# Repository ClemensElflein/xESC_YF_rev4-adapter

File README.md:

<!-- PROJECT SHIELDS -->
<!--
- Markdown "reference style" links for readability.
- Reference links are enclosed in brackets [ ] instead of parentheses ( ).
  (See the bottom of this document for the declaration of the reference variables)
-->
[![Contributors][contributors-shield]][contributors-url]
[![Forks][forks-shield]][forks-url]
[![Stargazers][stars-shield]][stars-url]
[![Issues][issues-shield]][issues-url]
[![MIT License][license-shield]][license-url]

<!-- PROJECT LOGO -->
<br />
<div align="center">
<h3 align="center">xESC YardForce (Rev4) adapter for <a href="https://github.com/ClemensElflein/OpenMower">OpenMower</a></h3>

  <p align="center">
    Simple xESC adapter for stock Rev4 (built 2017) blade-motor<br>
    (the one with a internal motor controller under his cap)
    <br />
  </p>

  |             v1.x Hardware              |             v2.x Hardware              |
  | :------------------------------------: | :------------------------------------: |
  |  |  |

</div>

<!-- ABOUT THE PROJECT -->
## About The Project

Those who want use <a href="https://github.com/ClemensElflein/OpenMower">OpenMower</a> with an older YardForce "Rev. 4" (built 2017) model, fail with the stock Blade-Motor as it has an embedded motor-controller under it's cap.

It's not very difficult to use this motor:
- Remove stock driver controller
- Wire the coil cables directly
- Add a 5 pin cable to the motor hall sensors
- Connect them to OM's mow-motor-hall-input plug
and use OM's xESC.

But it's somehow "crafted" and you need to be capable to do these things.

As an alternative, this "Adapter" is thought to replace OM's default Mow- xESC.<br>
In addition to this adapter, it's nevertheless **required to exchange two cables of the mow motor cabling**. But this should be also possible for the untalented (see [Requirements](#requirements)).

<p align="right">(<a href="#readme-top">back to top</a>)</p>

## Requirements

**It's mandatory to cross the green and black mow-motor-cables!**

> [!WARNING]  
> **Never** plug or un-plug the mow-motor while the adapter is powered!

> [!WARNING]  
> Do **not** simply trust the cable colors!<br>
> Check the image and validate if your
> cables do have the same colors! If not adapt accordingly

Either exchange the pins within the plug, or do it the lazy way like me, with a luster terminal.
The latter has the advantage that you immediately see that you already crossed green/black.

## Prerequisites

* The compiled firmware, which can be found within the [Actions](https://github.com/ClemensElflein/xESC_YF_rev4-adapter/actions) section. Click the one you're intersted in (newest or tagged), scroll down to 'Artifacts', download and unzip to somewhere.
* As of writing, your openmower image has to be on edge version >= commit [0bfd489](https://github.com/ClemensElflein/open_mower_ros/commit/0bfd489401b3e659d183e6c1f9b557cb0d59d3c1) which happened on 2024-07-04

## Firmware Installation

### Requirements

* You need an ST-Link debugger/programmer, like one of the cheap "ST-Link V2" probes from one of the big online retailer.
* [STLINK Tools](https://github.com/stlink-org/stlink) >= v1.8.0 (earlier versions do **not** support the used STM32C0x MCU)

### Hardware Version Branding

Starting with hardware version 2.0, the adapters MCU needs to be branded by flashing a hardware config into the OTP area.

#### Branding Process:

1. **Generate** Hardware Config Binaries

   ```bash
   cd firmware/host-hw-config
   lbuild build
   scons
   ```

   This creates i.e.:
   - `hw_config_v1.0.bin` - Hardware v1.0 configuration
   - `hw_config_v2.0.bin` - Hardware v2.0 configuration
  
1. **Connect your ST-Link** to the adapter PCB. Do **not** connect the 3.3V pin if your adapter is already assembled to the OpenMower Mainboard and get powered by it!

1. **Flash** Hardware Config

   ```bash
   # Flash/Brand v2.0 config with ST-Link/V2
   STM32_Programmer_CLI -c port=SWD -d hw_config_v2.0.bin 0x1FFF7000
   ```

The branding process writes a small hardware information structure to the first two OTP dwords. **Take attention** that OTP flash can be written only once!

**Important Notes:**
- Branding only needs as well as "can" be done only **once per device**
- The branding **truly survives firmware updates** (because OTP flash can be written only once)
- Hardware Version 1.x boards don't need branding. Non-branded devices get assumed to be v1.0 hardware
<br>
<br>

**Firmware Installation Variants**

We've two options to install the firmware. Either via:<br>
- ST-Link debugger/programmer, for which you need to have access to the adapter PCB's SWDIO pins, or via
- Open-Mower's UART via STM32 internal bootloader (which can be done with a closed mower)

### Firmware Installation via ST-Link debugger/programmer

#### Flash

1. Connect your ST-Link probe to the adapter PCB. Do **not** connect the 3.3V pin if your adapter is already assembled to the OpenMower Mainboard and get powered by it!

2. Flash the adapter:
   ```sh
   st-flash --reset write firmware_xesc_yf_rev4.bin 0x08000000
   ```
   When done, st-flash should report 'Flash written and verified! jolly good!' (or similar) and immediately reboot.<br>

   **Only relevant for v1.x hardware:**

   > [!WARNING]  
   > Do not unplug now!
   
   On absolutely first firmware boot, it need to flash some settings to the MCU. You'll see some blink codes.<br>
   Do NOT unplug till you see:
   - 3 simultaneous blinks of the green+red LED (=success), following of a
   - quick blink of the red LED (=no motor connected) as well as a
   - normal green blink (=ROS not connected).
   
   The whole procedure will only take about 10 seconds. Once the procedure got processed it don't get triggered again for this MCU on future firmware flashes.

   If the board doesn't come up with blink signs, unplug and replug it. But once you see blink signs, do **not** unplug it before getting the described LED codes of the previous paragraph.   

<p align="right">(<a href="#readme-top">back to top</a>)</p>

### Firmware Installation via serial connection (UART)

Firmware flashing via UART is currently only possible with OpenMower V1 based hardware!

#### Requirements

* [STM32CubeProgrammer](https://www.st.com/en/development-tools/stm32cubeprog.html) is the tool we need to flash via UART. But because we like to use it with our OpenMower's Raspberry-Pi, we need it in `aarch64` architecture. Unfortunately (as well as unbelievable) ST's programmer tool for ARM CPU's isn't available *for* ARM CPU's/architectures!!<br>
So we need to trick a little bit, and for this you need a non-arm Linux machine (x86_64).<br>
  1. Download [STM32CubePrg-Lin](https://www.st.com/en/development-tools/stm32cubeprog.html) package with (or to) a x86_64 Linux machine
  2. Unpack and install it on the x86_64 Linux machine
  3. Pack (zip, tar, ...) the installed binaries from where you just installed them
  4. Copy that package to your Raspberry-Pi and unpack it to somewhere. I placed mine to /opt/STM32CubeProgrammer
* [box64](https://github.com/ptitSeb/box64) to be able to run the STM32CubeProgrammer's x86_64 binary with our aarch64 architecture.<br>
Luckily they do have pre-build [Debian packages](https://github.com/ptitSeb/box64/blob/main/docs/COMPILE.md#debian-based-linux). Please follow their instruction.

Once *box64* got installed, you should be able to start the STM32Programmer CLI i.e. via: `/opt/STM32CubeProgrammer/bin/STM32_Programmer_CLI`

### Flash

1. Login to your OpenMower Raspberry-Pi and stop openmower:<br>
   `sudo systemctl stop openmower`
   
2. Configure Raspberry-PI's serial device where the adapter is connected to, which is normally */dev/ttyAMA3*:<br>
   `stty -F /dev/ttyAMA3 115200 raw`
   
3. Now trigger the current running adapter firmware to do a reboot into the bootloader via:<br>
    `echo -e "\x00Reboot into Bootloader" > /dev/ttyAMA3`

4. Check if STM32 MCU is now in bootloader mode (Step 3. was successful):<br>
   `/opt/STM32CubeProgrammer/bin/STM32_Programmer_CLI -c port=/dev/ttyAMA3`<br>
   Should output something like:<br>

   ```
      -------------------------------------------------------------------
                        STM32CubeProgrammer v2.16.0                  
      -------------------------------------------------------------------

   Serial Port /dev/ttyAMA3 is successfully opened.
   Port configuration: parity = even, baudrate = 115200, data-bit = 8,
                       stop-bit = 1.0, flow-control = off
   Activating device: OK
   Board       : --
   Chip ID: 0x443 
   BootLoader protocol version: 3.1
   Device name : STM32C01x
   Flash size  : 32 KBytes (default)
   Device type : MCU
   Revision ID : --  
   Device CPU  : Cortex-M0+
   ```

5. Flash:<br>
   `/opt/STM32CubeProgrammer/bin/STM32_Programmer_CLI -c port=/dev/ttyAMA3 -w firmware_xesc_yf_rev4.bin 0x08000000`

6. Reset the device (start our newly flashed program):<br>
   `/opt/STM32CubeProgrammer/bin/STM32_Programmer_CLI -c port=/dev/ttyAMA3 --go 0x08000000`

   **Only relevant for v1.x hardware:**

   > [!WARNING]  
   > Do not power-off now!
   
   On absolutely first firmware boot, it need to flash some settings to the MCU. You'll see some blink codes.<br>
   Do NOT unplug till you see:
   - 3 simultaneous blinks of the green+red LED (=success), following of a
   - quick blink of the red LED (=no motor connected) as well as a
   - normal green blink (=ROS not connected).
   
   The whole procedure will only take about 10 seconds. Once the procedure got processed it don't get triggered again for this MCU on future firmware flashes.

7. Finally start openmower again:<br>
   `sudo systemctl start openmower`

<p align="right">(<a href="#readme-top">back to top</a>)</p>

## OpenMower Config

### OpenMower V1 based Hardware (mower_config)

Lastly, you need to add the adapter to your mower_config. Here's the relevant section out of mower_config.sh.example:

```
# Select your ESC type
# Supported values as of today:
# xesc_mini: for the STM32 version (VESC)
# xesc_mini_w_r4ma: for the STM32 version (VESC), but with Rev4 (Mow) Motor Adapter (only available for YardForceSA650 mower type)
# xesc_2040: for the RP2040 version (very experimental!)
# xesc_2040_w_r4ma: for the RP2040 version (very experimental!), but with Rev4 (Mow) Motor Adapter (only available for YardForceSA650 mower type)
export OM_MOWER_ESC_TYPE="xesc_mini"
```

Once adapted, restart openmower via: `sudo systemctl restart openmower`

### OpenMower V2 based Hardware: (xCore Firmware)

Edit OpenMower stack config via `openmower configure env` and set `FIRMWARE="yardforce-v4"`

<p align="right">(<a href="#readme-top">back to top</a>)</p>

## LED codes

<table>
  <tr><th>Green</th><th>Red</th><th>Description</th></tr>
  <tr><td colspan="2" align="center">3 * quick blink</td><td>'Power up' successful</td></tr>
  <tr><td>1Hz blink</td><td></td><td>Waiting for init by xesc_ros</td></tr>
  <tr><td>0.5Hz flash<br>(short flash every 2 seconds)</td><td></td><td>Shutdown (Sleep) triggered by OpenMower Pico FW</td></tr>
  <tr><td>on</td><td></td><td>All fine (initialized, xesc_ros connected and no error)</td></tr>  
  <tr><td></td><td>1Hz blink</td><td>Waiting for OpenMower (xesc_ros driver) connect</td></tr>
  <tr><td></td><td>flash</td><td>One single short flash for every host communication error, like packet or CRC error</td></tr>
  <tr><td></td><td>on</td><td><b>Wrong hardware version firmware flashed!</b><br>Motor disabled for safety. Flash correct firmware</td></tr>
  <tr><td></td><td>5 * blink</td><td>NRST Pin not yet disabled. <b>Keep board powered</b> and watch for further LED codes</td></tr>
  <tr><td>5 * blink</td><td></td><td>NRST successful flashed</td></tr>
  <tr><td></td><td>4Hz quick blink</td><td>Open VMC (no motor connected).<br> <b>WARNING:</b> Do not connect the motor while the adapter is powered!</td></tr>
  <tr><td></td><td>2Hz fast blink</td><td>VMS temperature issue or over-current detected</td></tr>
</table>

<p align="right">(<a href="#readme-top">back to top</a>)</p>

## Self-Compile

This project is build with [modm](https://modm.io). You need to install the required toolchain as described in their [Installation](https://modm.io/guide/installation/) section, before going on.

Once done:

1. Clone this repository (inclusive submodules):<br>
  `git clone --recurse-submodules https://github.com/ClemensElflein/xESC_YF_rev4-adapter.git`
2. Change into the project source directory:<br>
  `cd xESC_YF_rev4-adapter/firmware/src`
3. Build the modm library files for a specific hardware version:<br>
   ```bash
   # This is for v2.0 hardware building
   lbuild -c hw-v2.xml build
   ```
4. Compile the firmware binary:<br>
  `scons [profile=<release|debug>] [build]`
5. Flash firmware:<br>
  For this, a specific [xPack OpenOCD](https://xpack-dev-tools.github.io/openocd-xpack/) version is required. Either install your own one, or use the one within the package folder by:<br>
  `export MODM_OPENOCD_BINARY=../packages/xpack-openocd-0.12.0-3-linux-x64/bin/openocd`<br>
  Afterwards flash the firmware via:<br>
  `scons program`

<p align="right">(<a href="#readme-top">back to top</a>)</p>

## Roadmap

(Ordered by priority)

- [x] Design schematics and PCB 
- [x] Produce PCB
- [ ] Firmware 
    - [x] Generic VM control (on/off)
    - [x] Generic motor control (start, stop, break)
    - [x] Read SA, math RPM
    - [x] Open VMC (no motor connected) detection
    - [x] Disable NRST pin functionality
    - [x] Motor current consumption
    - [x] PCB temperature (junction temp of STM)
    - [x] Support shutdown signal
    - [ ] ~~Stock motor (wrong) cabling detection~~
    - [x] STM32 bootloader / flash via UART support (OpenMower V1 based mainboard)
    - [ ] UART flash support for OpenMower V2 based carrier-boards
- [x] ROS driver
    - [x] xesc_ros::xesc_yfr4
    - [x] Add RPM
- [x] OpenMower Hardware V2 firmware driver

See the [open issues](https://github.com/ClemensElflein/xESC_YF_rev4-adapter/issues) for a full list of proposed features (and known issues).

<p align="right">(<a href="#readme-top">back to top</a>)</p>

## History

  | Version | Release Date | Info                                                                                                                                                                                          |
  | ------- | :----------: | --------------------------------------------------------------------------------------------------------------------------------------------------------------------------------------------- |
  | 0.3.0   |  2025-10-25  | - Fix "Open-Load" detection for Rev4-ESC hardware v1.0<br>- Improve load current and RPM calculations<br>- Add hardware/firmware mixup protection<br>- Add support for Rev4-ESC hardware v2.x |
  | 0.2.3   |  2024-10-03  | - Add RPM to status package                                                                                                                                                                   |
  | 0.2.2   |  2024-08-25  | - Support STM32 bootloader flash via UART                                                                                                                                                     |
  | 0.2.1   |  2024-08-19  | - Add shutdown signal handling (sleep/power-off VMC)<br>- Handle over-temp and over-current                                                                                                   |
  | 0.2.0   |  2024-08-16  | - Switch from Arduino to modm lib<br>- Integrate flash procedure to disable-NRST<br>- Add Motor current and PCB temperature                                                                   |
  | 0.1.1   |  2024-07-10  | - Open VMC (no motor connected) detection<br>- VMC-short and thermal error detection                                                                                                          |
  | 0.1.0   |  2024-07-05  | Generic functionality like Start, Stop, Break                                                                                                                                                 |

<p align="right">(<a href="#readme-top">back to top</a>)</p>

<!-- CONTRIBUTING -->
## Contributing

Contributions are what make the open source community such an amazing place to learn, inspire, and create. Any contributions you make are **greatly appreciated**.

If you have a suggestion that would make this better, please fork the repo and create a pull request. You can also simply open an issue with the tag "enhancement".
Don't forget to give the project a star! Thanks again!

1. Fork the Project
2. Create your Feature Branch (`git checkout -b feature/AmazingFeature`)
3. Commit your Changes (`git commit -m 'Add some AmazingFeature'`)
4. Push to the Branch (`git push origin feature/AmazingFeature`)
5. Open a Pull Request

<p align="right">(<a href="#readme-top">back to top</a>)</p>

<!-- LICENSE -->
## License

Distributed under the MIT License. See `LICENSE.txt` for more information.

<p align="right">(<a href="#readme-top">back to top</a>)</p>

<!-- CONTACT -->
## Contact

Project Link: [https://github.com/ClemensElflein/xESC_YF_rev4-adapter](https://github.com/ClemensElflein/xESC_YF_rev4-adapter)

<p align="right">(<a href="#readme-top">back to top</a>)</p>

<!-- MARKDOWN LINKS & IMAGES -->
<!-- https://www.markdownguide.org/basic-syntax/#reference-style-links -->
[contributors-shield]: https://img.shields.io/github/contributors/ClemensElflein/xESC_YF_rev4-adapter.svg?style=for-the-badge
[contributors-url]: https://github.com/ClemensElflein/xESC_YF_rev4-adapter/graphs/contributors
[forks-shield]: https://img.shields.io/github/forks/ClemensElflein/xESC_YF_rev4-adapter.svg?style=for-the-badge
[forks-url]: https://github.com/ClemensElflein/xESC_YF_rev4-adapter/network/members
[stars-shield]: https://img.shields.io/github/stars/ClemensElflein/xESC_YF_rev4-adapter.svg?style=for-the-badge
[stars-url]: https://github.com/ClemensElflein/xESC_YF_rev4-adapter/stargazers
[issues-shield]: https://img.shields.io/github/issues/ClemensElflein/xESC_YF_rev4-adapter.svg?style=for-the-badge
[issues-url]: https://github.com/ClemensElflein/xESC_YF_rev4-adapter/issues
[license-shield]: https://img.shields.io/github/license/ClemensElflein/xESC_YF_rev4-adapter.svg?style=for-the-badge
[license-url]: https://github.com/ClemensElflein/xESC_YF_rev4-adapter/blob/master/LICENSE.txt

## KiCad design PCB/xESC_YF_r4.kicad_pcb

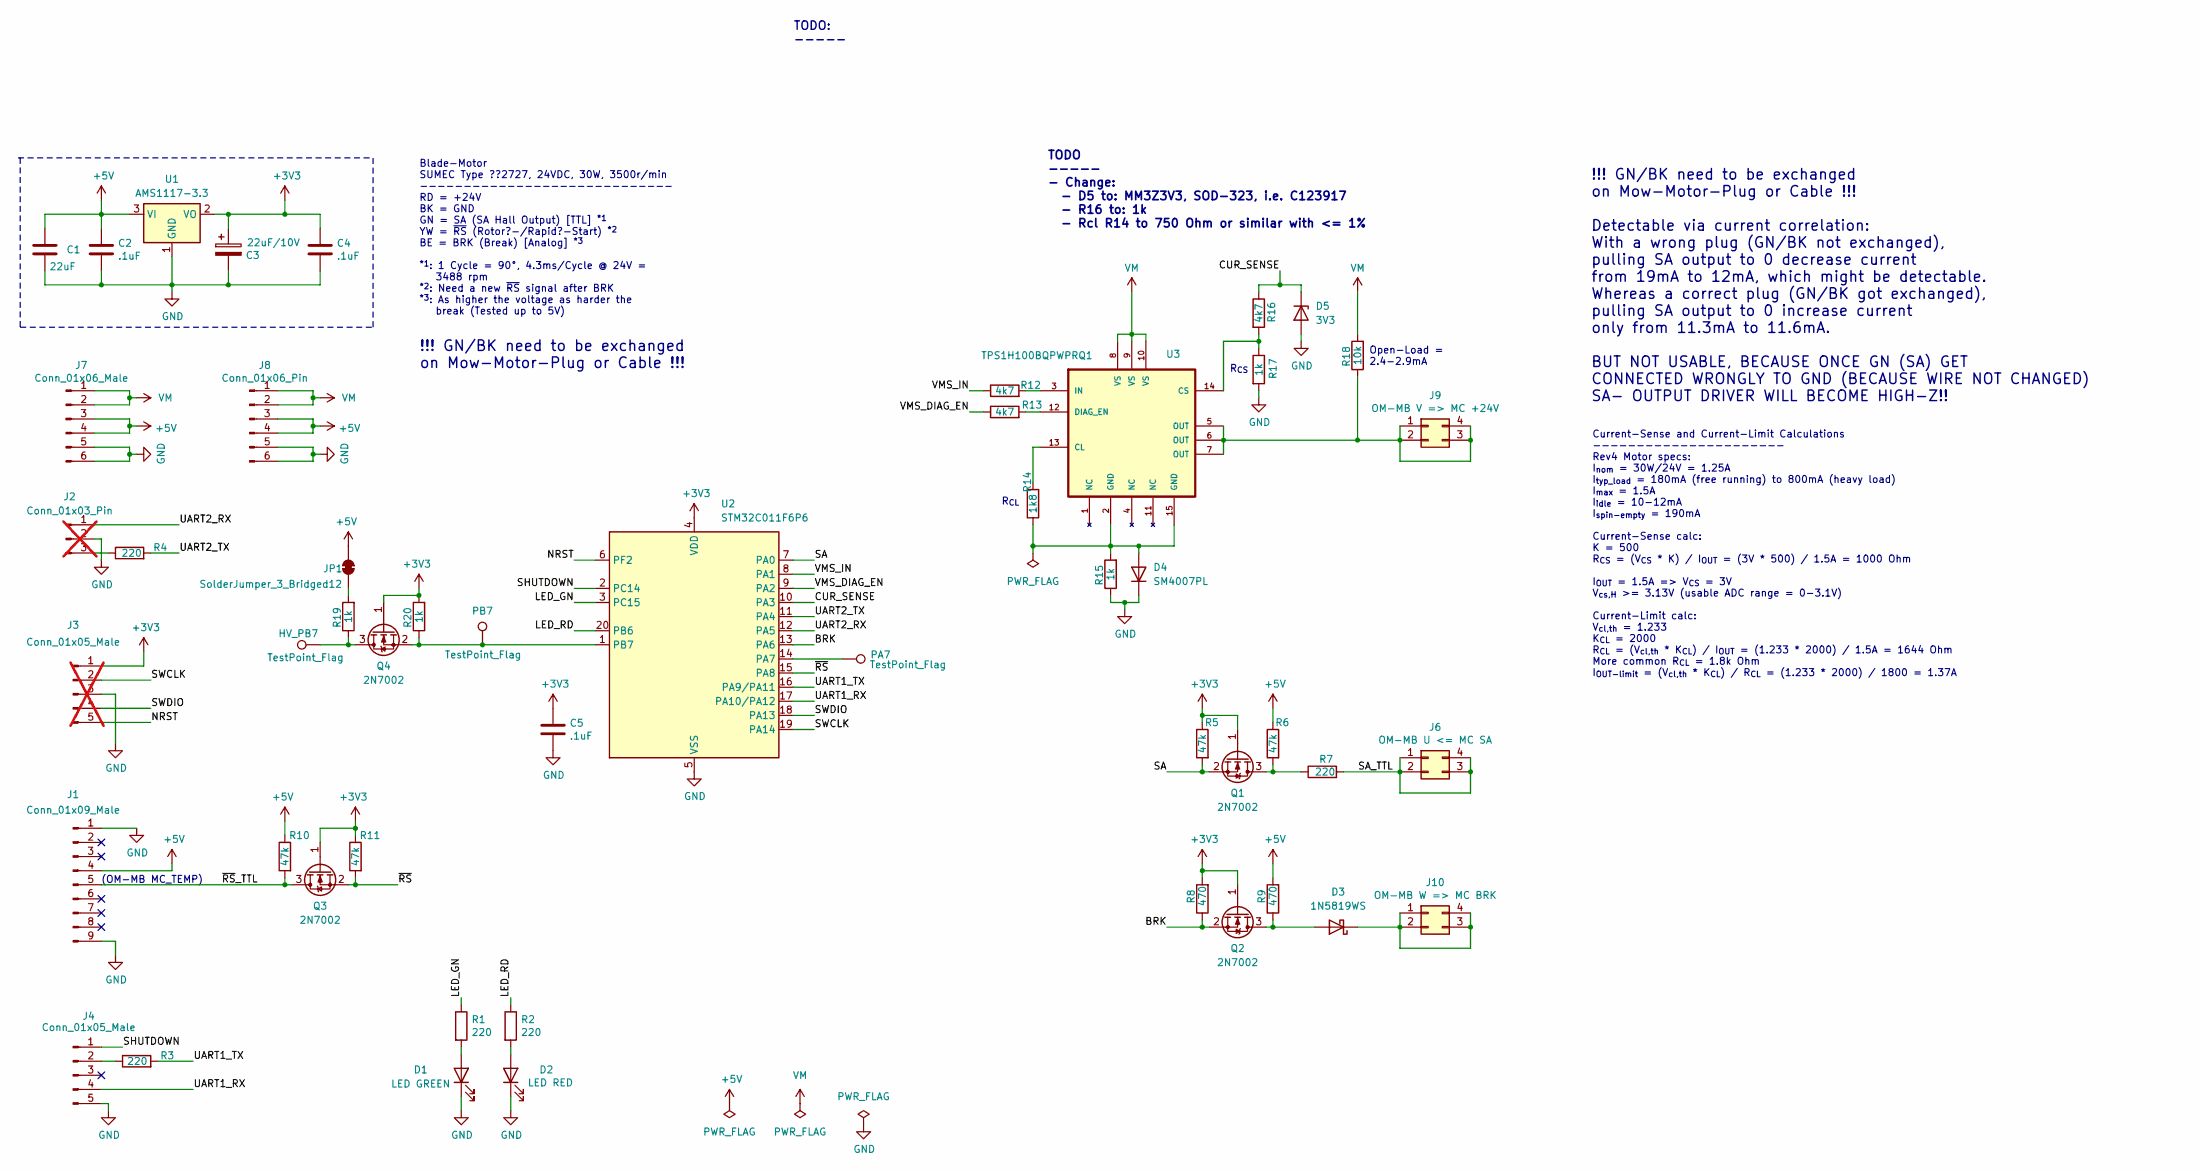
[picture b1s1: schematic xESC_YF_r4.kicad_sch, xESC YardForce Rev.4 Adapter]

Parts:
C1: 22uF; C_0805_2012Metric; LCSC C45783
C2, C4, C5: .1uF; C_0402_1005Metric; LCSC C1525
C3: 22uF/10V; CP_EIA-3216-10_Kemet-I; LCSC C129272
D1: LED GREEN; LED_0603_1608Metric; Part Number LTST-C191KGKT; Digikey 160-1446-1-ND
D2: LED RED; LED_0603_1608Metric; Part Number LTST-C191KRKT; Digikey 160-1447-1-ND
D3: 1N5819WS; D_SOD-323; LCSC C191023
D4: SM4007PL; D_SOD-123F; LCSC C64898
D5: 3V3; D_SOD-123F; MFR PART MMSZ4684T1G; LCSC C24672
HV_PB7: TestPoint_Flag; TestPoint_Pad_1.0x1.0mm
J1: Conn_01x09_Male; PinHeader_1x09_P2.54mm_Vertical; Part Number DZ254R-11-09-63; LCSC C2935915
J2: Conn_01x03_Pin; PinHeader_1x03_P2.54mm_Vertical; not fitted
J3: Conn_01x05_Male; PinHeader_1x05_P2.54mm_Vertical; Part Number DZ254R-11-05-63; LCSC C2935911; not fitted
J4: Conn_01x05_Male; PinHeader_1x05_P2.54mm_Vertical; Part Number DZ254R-11-05-63; LCSC C2935911
J6: OM-MB U <= MC SA; PinHeader_2x02_P2.54mm_Vertical; Part Number B-2100S04P-B110; LCSC C124362
J7: Conn_01x06_Male; PinHeader_1x06_P2.54mm_Vertical; Part Number DZ254R-11-06-63; LCSC C2935912
J8: Conn_01x06_Pin; PinHeader_1x06_P2.54mm_Vertical; Part Number DZ254R-11-06-63; LCSC C2935912
J9: OM-MB V => MC +24V; PinHeader_2x02_P2.54mm_Vertical; Part Number B-2100S04P-B110; LCSC C124362
J10: OM-MB W => MC BRK; PinHeader_2x02_P2.54mm_Vertical; Part Number B-2100S04P-B110; LCSC C124362
JP1: SolderJumper_3_Bridged12; SolderJumper-2_P1.3mm_Bridged_RoundedPad1.0x1.5mm
PA7: TestPoint_Flag; TestPoint_Pad_1.0x1.0mm
PB7: TestPoint_Flag; TestPoint_Pad_1.0x1.0mm
Q1, Q2, Q3, Q4: 2N7002; SOT-23; LCSC C8545
R1, R2, R7: 220; R_0603_1608Metric; LCSC C22962
R3, R4: 220; R_0603_1608Metric; Part Number 0603WAF2200T5E; LCSC C22962
R5, R6, R10, R11: 47k; R_0603_1608Metric; Part Number 0603WAF4702T5E; LCSC C25819
R8, R9: 470; R_0603_1608Metric; Part Number 0603WAF4700T5E; LCSC C23179
R12, R13, R16: 4k7; R_0603_1608Metric; Part Number 0603WAF4701T5E; LCSC C23162
R14: 1k8; R_0603_1608Metric; Part Number 0603WAF1801T5E; LCSC C4177
R15, R17, R19, R20: 1k; R_0603_1608Metric; Part Number 0603WAF1001T5E; LCSC C21190
R18: 10k; R_0603_1608Metric; Part Number 0603WAF1002T5E; LCSC C25804
U1: AMS1117-3.3; SOT-223-3_TabPin2; LCSC C6186
U2: STM32C011F6P6; TSSOP-20_4.4x6.5mm_P0.65mm; JLCPCB C5456198
U3: TPS1H100BQPWPRQ1; TPS1H100-Q1_ThermalVias; LCSC C475505

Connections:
+3V3: C3.1, C4.1, C5.1, J3.1, Q1.1 (G), Q2.1 (G), Q3.1 (G), Q4.1 (G), R5.1, R8.2, R11.1, R20.2, U1.2 (VO), U2.4 (VDD)
+5V: C1.1, C2.1, J1.4, J7.3, J7.4, J8.3, J8.4, JP1.2 (B), R6.1, R9.2, R10.1, U1.3 (VI)
/BRK: Q2.2 (S), R8.1, U2.13 (PA6)
/CUR_SENSE: D5.1 (K), R16.1, U2.10 (PA3)
/LED_GN: R1.1, U2.3 (PC15)
/LED_RD: R2.1, U2.20 (PB6)
/NRST: J3.5, U2.6 (PF2)
/SA: Q1.2 (S), R5.2, U2.7 (PA0)
/SA_TTL: J6.1, J6.2, J6.3, J6.4, R7.2
/SHUTDOWN: J4.1, U2.2 (PC14)
/SWCLK: J3.2, U2.19 (PA14)
/SWDIO: J3.4, U2.18 (PA13)
/UART1_RX: J4.4, U2.17 (PA10/PA12)
/UART1_TX: R3.2, U2.16 (PA9/PA11)
/UART2_RX: J2.1, U2.12 (PA5)
/UART2_TX: R4.2, U2.11 (PA4)
/VMS_DIAG_EN: R13.1, U2.9 (PA2)
/VMS_IN: R12.1, U2.8 (PA1)
/~RS: Q3.2 (S), R11.2, U2.15 (PA8)
/~RS_TTL: J1.5, Q3.3 (D), R10.2
GND: C1.2, C2.2, C3.2, C4.2, C5.2, D1.1 (K), D2.1 (K), D4.1 (K), D5.2 (A), J1.1, J1.9, J2.2, J3.3, J4.5, J7.5, J7.6, J8.5, J8.6, R15.1, R17.2, U1.1 (GND), U2.5 (VSS)
unnamed: D1.2 (A), R1.2
unnamed: D2.2 (A), R2.2
unnamed: D3.2 (A), Q2.3 (D), R9.1
unnamed: D3.1 (K), J10.1, J10.2, J10.3, J10.4
unnamed: D4.2 (A), R14.1, R15.2, U3.2 (GND), U3.15 (GND)
unnamed: J2.3, R4.1
unnamed: J4.2, R3.1
unnamed: J9.1, J9.2, J9.3, J9.4, R18.1, U3.5 (OUT), U3.6 (OUT), U3.7 (OUT)
unnamed: JP1.1 (A), R19.2
unnamed: Q1.3 (D), R6.2, R7.1
unnamed: HV_PB7.1, Q4.3 (D), R19.1
unnamed: PB7.1, Q4.2 (S), R20.1, U2.1 (PB7)
unnamed: PA7.1, U2.14 (PA7)
unnamed: R14.2, U3.13 (CL)
unnamed: R16.2, R17.1, U3.14 (CS)
unnamed: R13.2, U3.12 (DIAG_EN)
unnamed: R12.2, U3.3 (IN)
VM: J7.1, J7.2, J8.1, J8.2, R18.2, U3.8 (VS), U3.9 (VS), U3.10 (VS)

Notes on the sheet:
(OM-MB MC_TEMP)
Current-Sense and Current-Limit Calculations ---------------------- Rev4 Motor specs: I_{nom} = 30W/24V = 1.25A I_{typ_load} = 180mA (free running) to 800mA (heavy load) I_{max} = 1.5A I_{idle} = 10-12mA I_{spin-empty} = 190mA Current-Sense calc: K = 500 R_{CS} = (V_{CS} * K) / I_{OUT} = (3V * 500)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
TODO: -----
!!! GN/BK need to be exchanged on Mow-Motor-Plug or Cable !!! Detectable via current correlation: With a wrong plug (GN/BK not exchanged), pulling SA output to 0 decrease current from 19mA to 12mA, which might be detectable. Whereas a correct plug (GN/BK got exchanged), pulling SA output to 0 incre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
Open-Load = 2.4-2.9mA
Blade-Motor SUMEC Type ??2727, 24VDC, 30W, 3500r/min ----------------------------- RD = +24V BK = GND GN = SA (SA Hall Output) [TTL] ^{*1} YW = ~{RS} (Rotor?-/Rapid?-Start) ^{*2} BE = BRK (Break) [Analog] ^{*3} ^{*1}: 1 Cycle = 90°, 4.3ms/Cycle @ 24V = 3488 rpm ^{*2}: Need a new ~{RS} signal after 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
!!! GN/BK need to be exchanged on Mow-Motor-Plug or Cable !!!
TODO ----- - Change: - D5 to: MM3Z3V3, SOD-323, i.e. C123917 - R16 to: 1k - Rcl R14 to 750 Ohm or similar with <= 1%
R_{CL}
R_{CS}

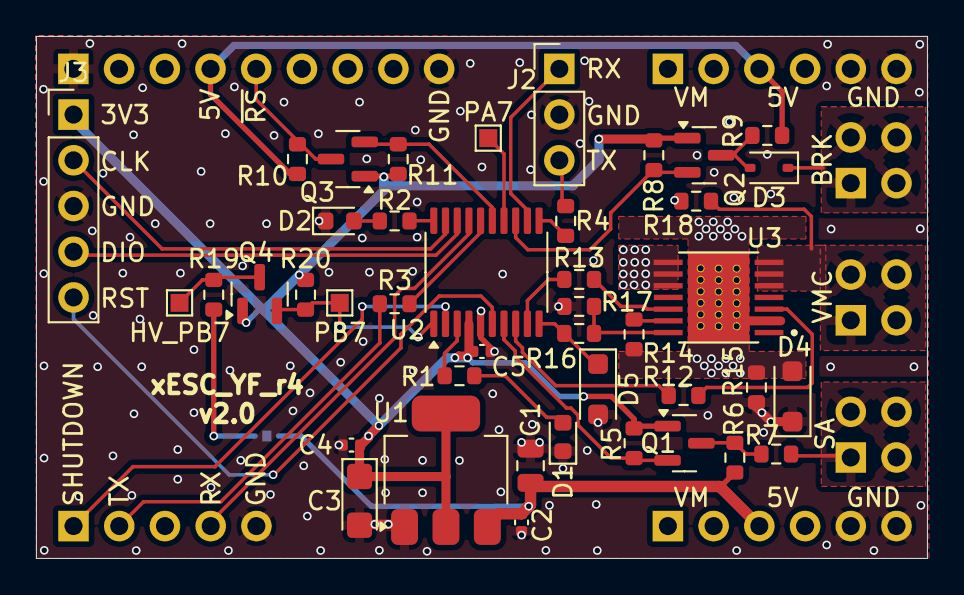
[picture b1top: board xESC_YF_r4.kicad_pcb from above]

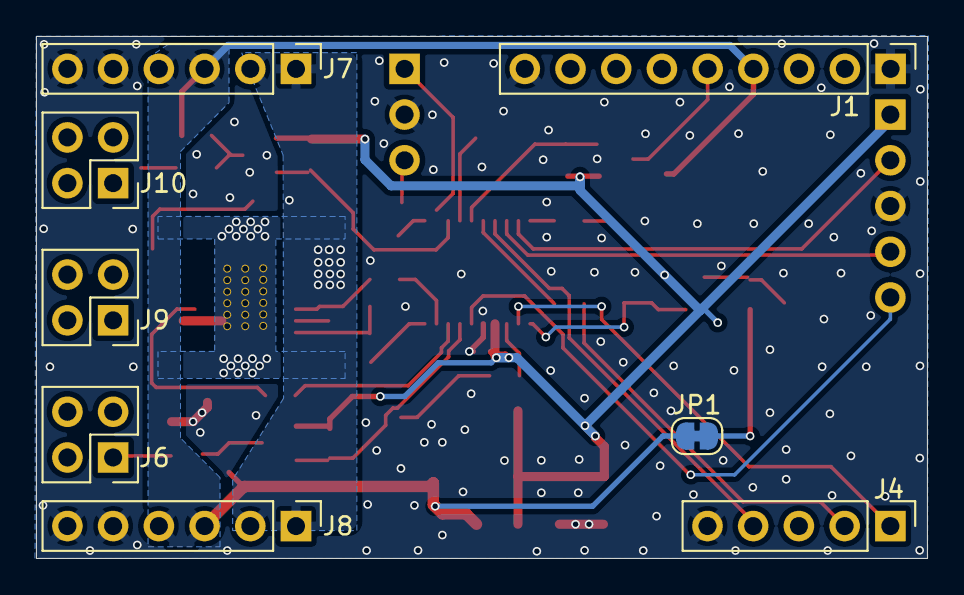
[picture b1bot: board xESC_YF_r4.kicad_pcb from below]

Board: 2 copper layers, 49.5 x 29.0 mm, 50 parts (8 on the bottom side), 39 nets.

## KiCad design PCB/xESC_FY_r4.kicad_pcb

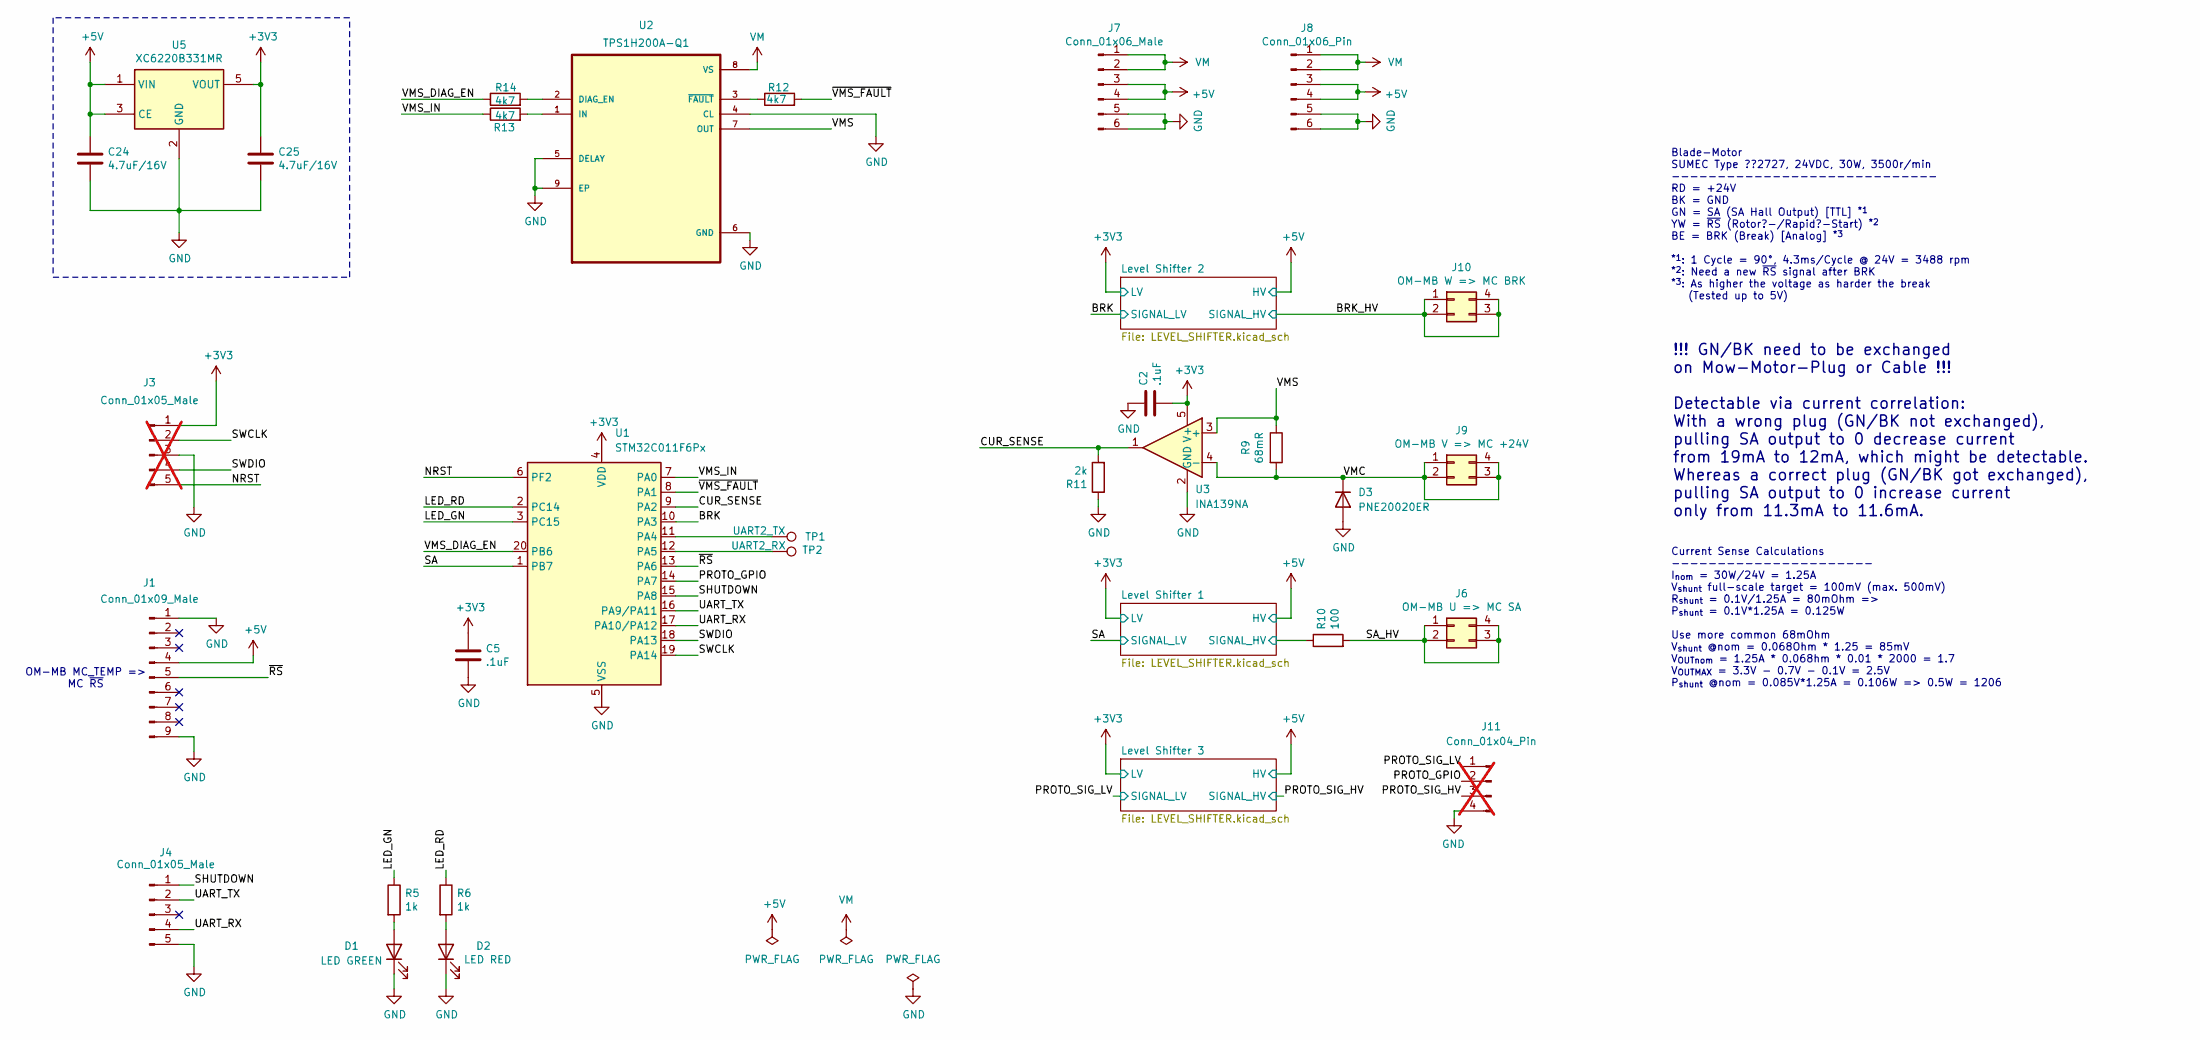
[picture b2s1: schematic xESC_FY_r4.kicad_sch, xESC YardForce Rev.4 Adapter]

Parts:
C2, C5: .1uF; C_0603_1608Metric; Part Number CL10B104KC8NNNC; Digikey 1276-1935-1-ND
C24, C25: 4.7uF/16V; C_0603_1608Metric; Part Number CL21A106KOQNNNE; Digikey 1276-1096-2-ND
D1: LED GREEN; LED_0603_1608Metric; Part Number LTST-C191KGKT; Digikey 160-1446-1-ND
D2: LED RED; LED_0603_1608Metric; Part Number LTST-C191KRKT; Digikey 160-1447-1-ND
D3: PNE20020ER; Nexperia_CFP3_SOD-123W
J1: Conn_01x09_Male; PinHeader_1x09_P2.54mm_Vertical; Part Number DZ254R-11-09-63; LCSC C2935915
J3: Conn_01x05_Male; PinHeader_1x05_P2.54mm_Vertical; Part Number DZ254R-11-05-63; LCSC C2935911; not fitted
J4: Conn_01x05_Male; PinHeader_1x05_P2.54mm_Vertical; Part Number DZ254R-11-05-63; LCSC C2935911
J6: OM-MB U => MC SA; PinHeader_2x02_P2.54mm_Vertical; Part Number B-2100S04P-B110; LCSC C124362
J7: Conn_01x06_Male; PinHeader_1x06_P2.54mm_Vertical; Part Number DZ254R-11-06-63; LCSC C2935912
J8: Conn_01x06_Pin; PinHeader_1x06_P2.54mm_Vertical; Part Number DZ254R-11-06-63; LCSC C2935912
J9: OM-MB V => MC +24V; PinHeader_2x02_P2.54mm_Vertical; Part Number B-2100S04P-B110; LCSC C124362
J10: OM-MB W => MC BRK; PinHeader_2x02_P2.54mm_Vertical; Part Number B-2100S04P-B110; LCSC C124362
J11: Conn_01x04_Pin; PinHeader_1x04_P2.54mm_Vertical; not fitted
R5, R6: 1k; R_0603_1608Metric; Part Number RC0603FR-07150RL; Digikey 311-150HRCT-ND
R9: 68mR; R_1206_3216Metric_Pad1.30x1.75mm_HandSolder; Part Number KDV12FR068ET; JLCPCB C2442650
R10: 100; R_0603_1608Metric
R11: 2k; R_0603_1608Metric
R12, R13, R14: 4k7; R_0603_1608Metric; Part Number RC0603FR-07150RL; Digikey 311-150HRCT-ND
TP1: UART2_TX; TestPoint_Pad_1.5x1.5mm
TP2: UART2_RX; TestPoint_Pad_1.5x1.5mm
U1: STM32C011F6Px; TSSOP-20_4.4x6.5mm_P0.65mm
U2: TPS1H200A-Q1; SOP65P490X110-9N-AHMOD
U3: INA139NA; SOT-23-5
U5: XC6220B331MR; SOT-23-5; Part Number XC6220B331MR; Digikey 893-1133-1-ND

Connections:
+3V3: C2.2, C5.1, C25.1, J3.1, U1.4 (VDD), U3.5 (V+), U5.5 (VOUT); also elsewhere on the board
+5V: C24.1, J1.4, J7.3, J7.4, J8.3, J8.4, U5.1 (VIN), U5.3 (CE); also elsewhere on the board
/BRK: U1.10 (PA3); also elsewhere on the board
/BRK_HV: J10.1, J10.2, J10.3, J10.4; also elsewhere on the board
/CUR_SENSE: R11.2, U1.9 (PA2), U3.1
/LED_GN: R5.1, U1.3 (PC15)
/LED_RD: R6.1, U1.2 (PC14)
/Level Shifter 1/SIGNAL_HV: R10.1; also elsewhere on the board
/NRST: J3.5, U1.6 (PF2)
/PROTO_GPIO: J11.2, U1.14 (PA7)
/PROTO_SIG_HV: J11.3; also elsewhere on the board
/PROTO_SIG_LV: J11.1; also elsewhere on the board
/SA: U1.1 (PB7); also elsewhere on the board
/SA_HV: J6.1, J6.2, J6.3, J6.4, R10.2
/SHUTDOWN: J4.1, U1.15 (PA8)
/SWCLK: J3.2, U1.19 (PA14)
/SWDIO: J3.4, U1.18 (PA13)
/UART_RX: J4.4, U1.17 (PA10/PA12)
/UART_TX: J4.2, U1.16 (PA9/PA11)
/VMC: D3.1 (K), J9.1, J9.2, J9.3, J9.4, R9.2, U3.4 (-)
/VMS: R9.1, U2.7 (OUT), U3.3 (+)
/VMS_DIAG_EN: R14.1, U1.20 (PB6)
/VMS_IN: R13.1, U1.7 (PA0)
/~RS: J1.5, U1.13 (PA6)
/~VMS_FAULT: R12.2, U1.8 (PA1)
GND: C2.1, C5.2, C24.2, C25.2, D1.1 (K), D2.1 (K), D3.2 (A), J1.1, J1.9, J3.3, J4.5, J7.5, J7.6, J8.5, J8.6, J11.4, R11.1, U1.5 (VSS), U2.4 (CL), U2.5 (DELAY), U2.6 (GND), U2.9 (EP), U3.2 (GND), U5.2 (GND)
unnamed: D1.2 (A), R5.2
unnamed: D2.2 (A), R6.2
unnamed: TP1.1, U1.11 (PA4)
unnamed: TP2.1, U1.12 (PA5)
unnamed: R14.2, U2.2 (DIAG_EN)
unnamed: R13.2, U2.1 (IN)
unnamed: R12.1, U2.3 (~FAULT)
VM: J7.1, J7.2, J8.1, J8.2, U2.8 (VS)

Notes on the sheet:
OM-MB MC_TEMP => MC ~{RS}
Blade-Motor SUMEC Type ??2727, 24VDC, 30W, 3500r/min ----------------------------- RD = +24V BK = GND GN = SA (SA Hall Output) [TTL] ^{*1} YW = ~{RS} (Rotor?-/Rapid?-Start) ^{*2} BE = BRK (Break) [Analog] ^{*3} ^{*1}: 1 Cycle = 90°, 4.3ms/Cycle @ 24V = 3488 rpm ^{*2}: Need a new ~{RS} signal after 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
!!! GN/BK need to be exchanged on Mow-Motor-Plug or Cable !!! Detectable via current correlation: With a wrong plug (GN/BK not exchanged), pulling SA output to 0 decrease current from 19mA to 12mA, which might be detectable. Whereas a correct plug (GN/BK got exchanged), pulling SA output to 0 incre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
Current Sense Calculations ---------------------- I_{nom} = 30W/24V = 1.25A V_{shunt} full-scale target = 100mV (max. 500mV) R_{shunt} = 0.1V/1.25A = 80mOhm => P_{shunt} = 0.1V*1.25A = 0.125W Use more common 68mOhm V_{shunt} @nom = 0.068Ohm * 1.25 = 85mV V_{OUTnom} = 1.25A * 0.068hm * 0.01 * 2000 =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

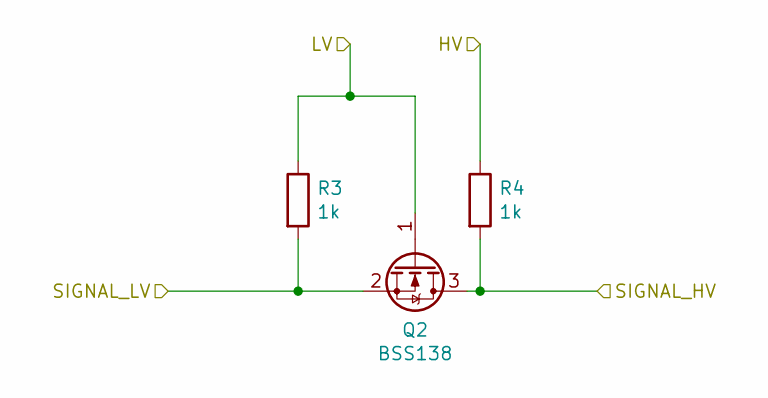
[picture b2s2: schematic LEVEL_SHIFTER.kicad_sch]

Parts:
Q2: BSS138; SOT-23; Part Number AP2300; LCSC C3040446
R3, R4: 1k; R_0805_2012Metric_Pad1.20x1.40mm_HandSolder; Part Number RC0805FR-071KL; Digikey 311-1.00KCRCT-ND

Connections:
+3V3: Q2.1 (G), R3.1; also elsewhere on the board
+5V: R4.1; also elsewhere on the board
/BRK: Q2.2 (S), R3.2; also elsewhere on the board
/BRK_HV: Q2.3 (D), R4.2; also elsewhere on the board

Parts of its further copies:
Q1, Q3: BSS138; SOT-23; Part Number AP2300; LCSC C3040446
R1, R2, R7, R8: 1k; R_0805_2012Metric_Pad1.20x1.40mm_HandSolder; Part Number RC0805FR-071KL; Digikey 311-1.00KCRCT-ND

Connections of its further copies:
+3V3: Q1.1 (G), Q3.1 (G), R1.1, R7.1; also elsewhere on the board
+5V: R2.1, R8.1; also elsewhere on the board
/Level Shifter 1/SIGNAL_HV: Q1.3 (D), R2.2; also elsewhere on the board
/PROTO_SIG_HV: Q3.3 (D), R8.2; also elsewhere on the board
/PROTO_SIG_LV: Q3.2 (S), R7.2; also elsewhere on the board
/SA: Q1.2 (S), R1.2; also elsewhere on the board

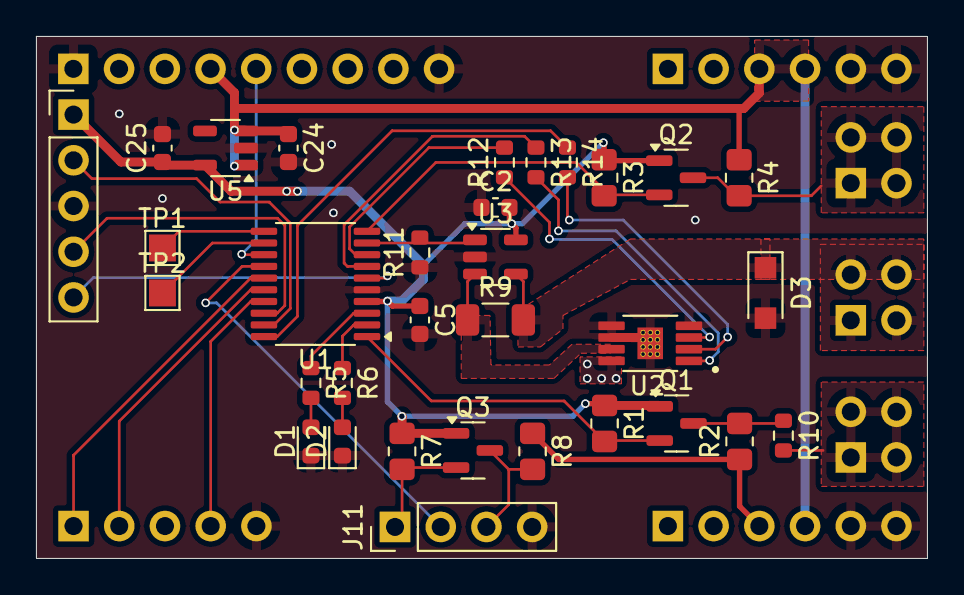
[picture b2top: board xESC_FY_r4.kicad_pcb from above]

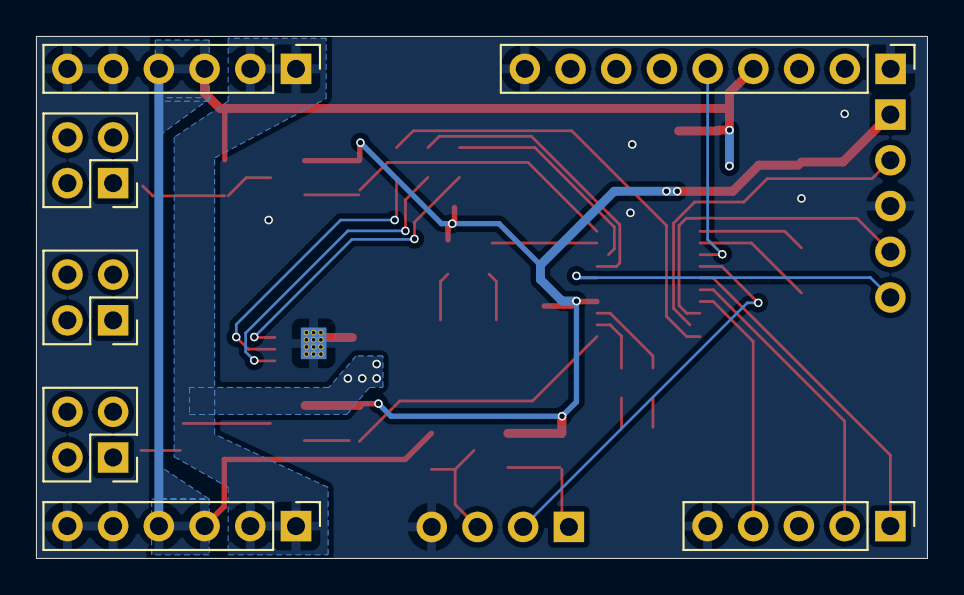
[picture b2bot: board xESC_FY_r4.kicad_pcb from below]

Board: 2 copper layers, 49.5 x 29.0 mm, 39 parts (7 on the bottom side), 34 nets.

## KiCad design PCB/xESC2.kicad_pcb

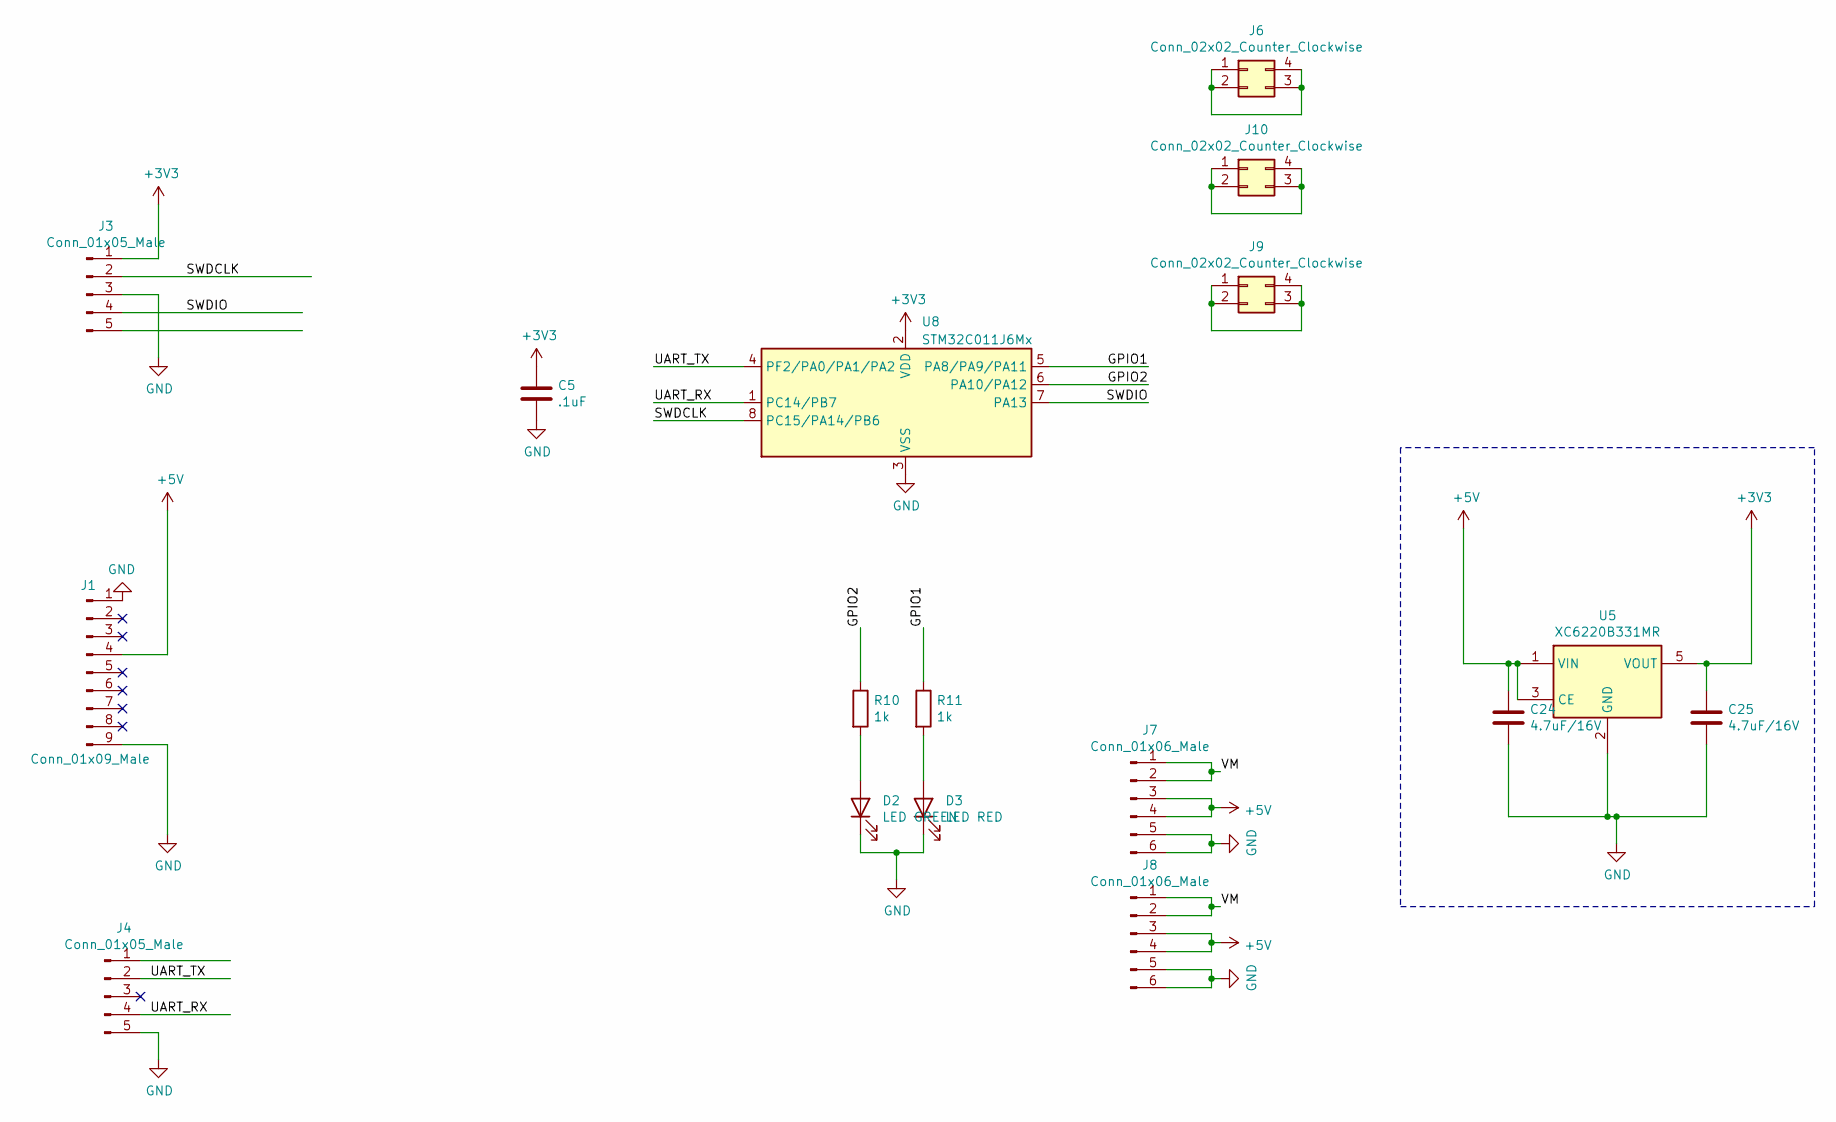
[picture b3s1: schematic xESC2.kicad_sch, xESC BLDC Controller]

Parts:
C5: .1uF; C_0603_1608Metric; Part Number CL10B104KC8NNNC; Digikey 1276-1935-1-ND
C24, C25: 4.7uF/16V; C_0603_1608Metric; Part Number CL21A106KOQNNNE; Digikey 1276-1096-2-ND
D2: LED GREEN; LED_0603_1608Metric; Part Number LTST-C191KGKT; Digikey 160-1446-1-ND
D3: LED RED; LED_0603_1608Metric; Part Number LTST-C191KRKT; Digikey 160-1447-1-ND
J1: Conn_01x09_Male; PinHeader_1x09_P2.54mm_Vertical; Part Number DZ254R-11-09-63; LCSC C2935915
J3, J4: Conn_01x05_Male; PinHeader_1x05_P2.54mm_Vertical; Part Number DZ254R-11-05-63; LCSC C2935911
J6, J9, J10: Conn_02x02_Counter_Clockwise; PinHeader_2x02_P2.54mm_Vertical; Part Number B-2100S04P-B110; LCSC C124362
J7, J8: Conn_01x06_Male; PinHeader_1x06_P2.54mm_Vertical; Part Number DZ254R-11-06-63; LCSC C2935912
R10, R11: 1k; R_0603_1608Metric; Part Number RC0603FR-07150RL; Digikey 311-150HRCT-ND
U5: XC6220B331MR; SOT-23-5; Part Number XC6220B331MR; Digikey 893-1133-1-ND
U8: STM32C011J6Mx; SOIC-8_3.9x4.9mm_P1.27mm

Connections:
+3V3: C5.1, C25.1, J3.1, U5.5 (VOUT), U8.2 (VDD)
+5V: C24.1, J1.4, J7.3, J7.4, J8.3, J8.4, U5.1 (VIN), U5.3 (CE)
/GPIO1: R11.1, U8.5 (PA8/PA9/PA11)
/GPIO2: R10.1, U8.6 (PA10/PA12)
/SWDCLK: J3.2, U8.8 (PC15/PA14/PB6)
/SWDIO: J3.4, U8.7 (PA13)
/UART_RX: J4.4, U8.1 (PC14/PB7)
/UART_TX: J4.2, U8.4 (PF2/PA0/PA1/PA2)
/VM: J7.1, J7.2, J8.1, J8.2
GND: C5.2, C24.2, C25.2, D2.1 (K), D3.1 (K), J1.1, J1.9, J3.3, J4.5, J7.5, J7.6, J8.5, J8.6, U5.2 (GND), U8.3 (VSS)
unnamed: D2.2 (A), R10.2
unnamed: D3.2 (A), R11.2
unnamed: J6.1, J6.2, J6.3, J6.4
unnamed: J9.1, J9.2, J9.3, J9.4
unnamed: J10.1, J10.2, J10.3, J10.4

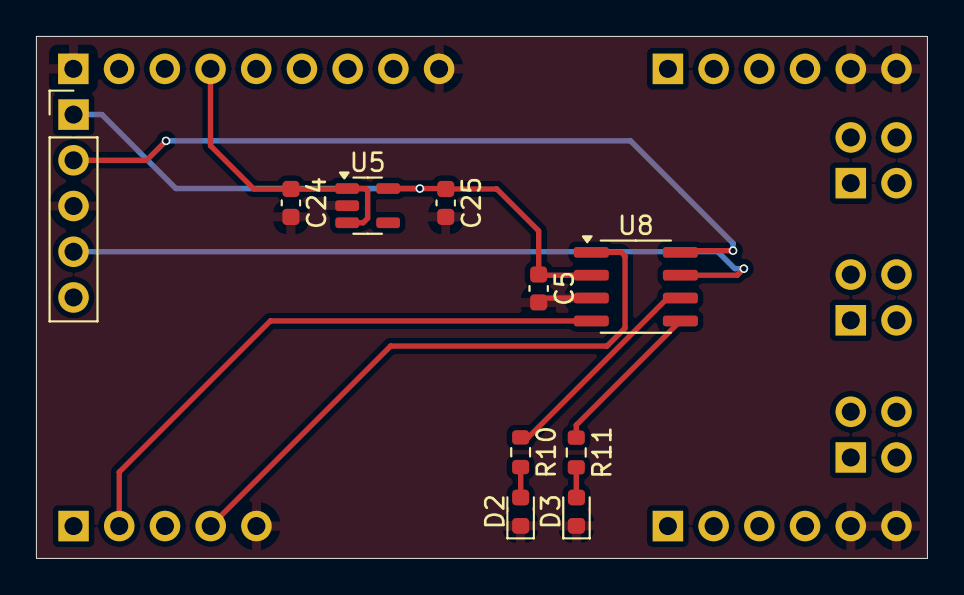
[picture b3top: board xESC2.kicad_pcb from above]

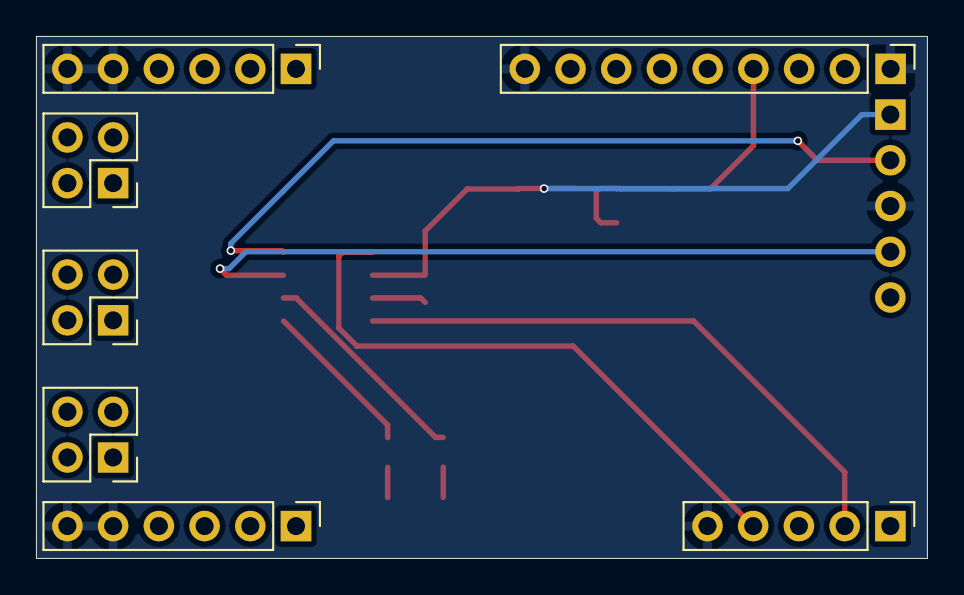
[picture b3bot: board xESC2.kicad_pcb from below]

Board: 4 copper layers, 49.5 x 29.0 mm, 17 parts (7 on the bottom side), 15 nets.

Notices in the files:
README.md:
License:
Distributed under the MIT License. See `LICENSE.txt` for more information.
PCB/v1.0/xESC_YF_r4.kicad_sch:
Creative Commons Attribution-NonCommercial-ShareAlike 4.0 International License.
Licensed under
